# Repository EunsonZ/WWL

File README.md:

# WWL 知识库

本库帮助学习者追踪问题中的对象、关系、证据和条件：先形成可以预测现象的直觉，再理解推导或论证，最后在条件改变后重新判断。数学证明、程序执行、历史解释和规范性选择各有自己的依据；学科入口保留独立的深入路线。

从一个知识域的首页进入，再按其中的课程地图（MOC）选择阅读顺序。课程正文、可运行实验与来源材料各有入口；无需按文件夹编号一次读完整个库。

按问题进入：[[00-工作台/按问题找知识|问题入口]] · 日常记录：[[00-工作台/README|工作台]] · 浏览筛选：[[00-工作台/知识目录.base|知识目录]]

先挑一个具体问题：

| 你想弄清什么 | 先读哪里，带回什么 |
| --- | --- |
| 税在商家缴，为什么买卖双方都可能承担？ | [[社会科学/40-公共政策与社会学/02-税收转移公共服务与归宿#线性供需手算\|税楔与线性供需]]：沿同一买方价、卖方价和交易量复算归宿，再检查法定责任与福利的区别。 |
| 张量中的 1.5 怎样成为可靠的位串，又怎样交给线程？ | [[计算机知识/40-并行与异构计算/80-张量跨层执行/01-同一张量从数值到线程\|同一数值的跨层路线]]：分清数学值、编码、存储和执行；需要器件层时，从文中的本库 CMOS/噪声支线继续。 |
| 工资、贷款、进口与公共决定怎样改变生活？ | [[社会科学/00-开始/01-社会认知学习路线与32个问题\|社会认知八组问题]]：选择组织、制度、税收预算、货币金融或国内外循环，不以考试年度为前置。 |

普通 Markdown 和链接提供完整阅读入口；知识目录、Bases 与 Canvas 只是可选视图。

如果你想把机器学习、系统与算法的基础连成一条可返回的阅读路径，使用 [[00-工作台/基础理论学习路线|基础理论学习路线]]；它只帮你选择下一页，不把阅读次数或时间当作掌握证明。

## 从这里开始

| 知识域 | 首页 | 继续阅读 |
| --- | --- | --- |
| 数学 | [[数学/00-数学-首页\|数学首页]] | [[数学/01-数学学习路线\|学习路线]] · [[数学/02-AI数学应用索引\|AI 数学应用索引]] |
| AI | [[AI/00-开始/00-AI-首页\|AI 首页]] | [[AI/00-开始/05-问题驱动知识图谱与难点导航\|按问题寻找入口]] · [[AI/80-实践/00-AI实践-MOC\|实践地图]] |
| 计算机知识 | [[计算机知识/00-开始/00-计算机知识-首页\|计算机首页]] | [[计算机知识/00-开始/全局导航/00-总学习地图\|总学习地图]] · [[计算机知识/Kali/00-导航与方法/00-Kali知识地图\|Kali 知识地图]] |
| 编程知识 | [[编程知识/00-开始/00-编程知识-首页\|编程知识首页]] | [[编程知识/10-基础/01-正则表达式/00-正则表达式-MOC\|正则表达式]]；语言系统课程从计算机首页进入 |
| 哲学与文化 | [[哲学与文化/00-开始/00-哲学与文化-首页\|哲学与文化首页]] | [[哲学与文化/10-主题/01-文化政治与组织结构/00-文化政治与组织结构-MOC\|文化政治与组织结构]] |
| 社会科学 | [[社会科学/00-开始/00-社会科学-首页\|社会科学首页]] | [[社会科学/20-经济流动与宏观/00-经济流动与宏观-MOC\|经济流动与宏观]] · [[社会科学/30-金融市场与风险/00-金融市场与风险-MOC\|金融市场与风险]] · [[社会科学/40-公共政策与社会学/00-公共政策与社会学-MOC\|公共政策与社会学]] |
| 物理 | [[物理/00-开始/00-物理-首页\|物理首页]] | [[物理/20-电磁学/00-电磁学-MOC\|场源与边值]] · [[物理/30-电动力学/00-电动力学-MOC\|守恒源与因果场]] · [[物理/40-量子力学/00-量子力学-MOC\|态、谱与测量]] · [[物理/50-半导体物理/00-半导体物理-MOC\|晶体、占据与输运]] |
| 电子电路 | [[电子电路/00-开始/00-电子电路-首页\|电子电路首页]] | [[电子电路/10-电路基础/00-电路基础-MOC\|单位、KCL与RC]] · [[电子电路/00-开始/01-电子电路课程地图与覆盖边界\|E01–E12分层范围]] · [[电子电路/10-电路基础/00-电路基础-MOC#从五课接到器件与模拟\|五课后进入器件与模拟]] · [[电子电路/20-器件与模拟/01-PN结与二极管工作点\|旧版二极管工作点速查]] |
| 信号与系统 | [[信号与系统/00-开始/00-信号与系统-首页\|信号与系统首页]] | [[信号与系统/10-连续与离散系统/00-连续与离散系统-MOC\|对象、卷积、ROC与采样]] · [[信号与系统/00-开始/01-信号系统课程地图与覆盖边界\|S01–S14与控制方向]] · [[信号与系统/20-数字信号处理/01-FIR滤波设计与频率规格\|滤波与流式]] · [[信号与系统/30-随机信号与推断/01-随机过程相关与功率谱\|随机谱与检测]] |
| 控制论 | [[控制论/00-控制论-MOC\|控制课程入口]] | [[控制论/00-开始/01-控制课程路线与覆盖边界\|调节起点与课程路线]] · [[控制论/10-系统课程/01-调节目标信息与行动#先做一个无需微积分的诊断\|信息、动作与合格目标]] · [[控制论/10-系统课程/02-热模型从物理到连续反馈#先固定对象和每个端口\|带单位的热模型]] |
| Obsidian 知识 | [[Obsidian知识/00-开始/Welcome\|Obsidian 教学首页]] | [[Obsidian知识/00-开始/00-Playground-首页\|练习地图]] · [[Obsidian知识/00-开始/02-30分钟快速上手\|30 分钟上手]] |

各知识域保留基础和深入路径；Obsidian 是阅读、记录与工具支撑层。物理四课从各自已建段落进入，电子路线继续承担端口、器件与工程近似；各域剩余课程、专业工具、设备和真人证据按对应正文分别判断。

## 实践、材料与任务

- 计算机实验与图示：[[计算机知识/00-开始/全局导航/09-本地实验与验证入口|实验入口]]、[[计算机知识/00-开始/全局导航/08-本地图示索引|图示索引]]。
- 数学资源与记号：[[数学/90-资源/00-数学资源-MOC|数学资源地图]]。
- 哲学原始材料及两份稿件：[[哲学与文化/90-资源/01-原始材料与参考来源索引|来源索引]]；[[Clippings/分析文化政治影响|原始对话]]。
- 书籍与历史个人资料：[[资料/README|资料总索引]]；数学、物理、电子与信号、钢琴书籍及个人规划分区阅读。
- 双来源原稿：[[Clippings/WorkWithLLM/原稿索引|WorkWithLLM 对话与草稿]]、[[Clippings/AGoodStart101/原稿索引|AGoodStart101 教程与剪藏]]。
- 已有任务工作区：[[TaskNotes/Start Here|TaskNotes 入口]]。

## 维护与阅读说明

日常使用不需要管理 agents。把具体卡点交给 AI 即可，例如“这页的公式怎样代入”“两篇解释是不是矛盾”“我记得这个概念，但找不到”。AI 负责定位、必要分工、证据与检查，不要求你维护任务表。

知识维护见 [[00-工作台/维护指南|维护指南]]；多人交接、模型与费用见 [[00-工作台/并行协作与模型路由|并行协作与模型路由]]；AI 的稳定入口是 [[AGENTS|协作约定]]。插件日常与按需使用见 [[00-工作台/插件取舍|插件取舍]]，实际改进、验证和未决项从 [[CHANGES|CHANGES.md]] 进入。

[[NewAgents|旧手册入口]] 只供追溯。当前建设与未决项从 [任务总入口 #224](https://github.com/EunsonZ/WWL/issues/224) 进入对应议题，目录整理由 [#251](https://github.com/EunsonZ/WWL/issues/251) 接续；旧执行单和规划按固定提交追溯。历史交付只证明当时明示的范围，不替当前快照认证。

资料书目中的“本包未提供”表示附件不在上传快照中，不能用空文件冒充恢复。内容可读、证据已核验、个人已掌握是不同状态；并行数量也不是质量证明。

## 历史导入与结构记录

- 双来源增量导入、保全与验证范围见 [[Logs/2026-09-08_双来源知识增量导入/验收记录|增量导入验收记录]]。
- 前一批目录变更、历史路径和缺失材料见 [[Logs/2026-09-08_TBM结构整理/验收记录|结构整理记录]]。
- 历史说明中的“本库未收录”表示原引用的材料不在当时库中，原目标保留以便追溯；历史报告只说明对应快照。

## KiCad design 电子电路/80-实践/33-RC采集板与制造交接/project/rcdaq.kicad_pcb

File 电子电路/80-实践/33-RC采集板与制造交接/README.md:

---
stage: 2
aliases: []
sources:
  - https://docs.kicad.org/9.0/en/cli/cli.html
  - https://dev-docs.kicad.org/en/file-formats/sexpr-schematic/
prerequisites:
  - "[[电子电路/50-PCB布局与调试/01-符号引脚封装与BOM替代#先确定电路，再决定空间]]"
  - "[[电子电路/50-PCB布局与调试/05-KiCad项目到制造包与人工复核#ERC和DRC回答不同问题]]"
---
# RCDAQ-P1：同一板、不同证据层

基础入口按J1→R1→OUT→C1/R2→GND手算1V加载；快进入口核21焊盘、4网、27前层segments、5地via的几何图与采样电荷/频率阻抗边界。全部模型和图对应同一原创40×30mm无源板，ADC在J2外部，没有假装板上IC/MCU存在。

## 文件与版本

board.json是教学坐标/引脚/路由合同；project有rcdaq.kicad_pro/sch/pcb，自有symbol/footprint库与librarytables、rcdaq.net、bom.csv/testpoints.csv、fabrication-checklist。原生格式候选可编辑但本机未发现kicad-cli，真实软件parse/save、ERC/DRC、B.Cu填区、Gerber/钻孔导出尚未运行。CPU解析只是有限s-expression字段与网集核对。采购MPN全部UNSELECTED；自有0805等几何尚未经实际MPN/厂商规则核，不能送厂。教学源文件generator标wwl_pcb1，未伪装成eeschema/pcbnew写出的工具产物。

源pcb_model.py/test_pcb_model.py/generate_figures.py各只一真源，不创建重复code-sync副本；原库与他人源码未动。SVG是真源生成输出，360/425PNG从同SVG渲染，图是原创教学模型，不是实际CAD截图/照片/仪器读数。

## 有限API及物理合同

模型只接受Python原生int/float实数，拒bool/complex/数组/cast对象及非有限；先校验再算，不静默丢虚部。标量支持域刻意有限：t0..100s、source/initial0..3.3V、R/load/probe1..1e9/1e12Ω、C1pF..10mF。rc保持v(0)=initial，expm1计算小时间步，明确load与probe并联；返回V、τ(s)、pole(Hz)、gain无量纲，t非常大视为稳态指数衰减。

sharing/coupling按指定初态电荷守恒，不是实测ADC参数；内部C1fF..1mF、crossC1fF..1μF，外C1pF..10mF，电压/edge±3.3V合同分别校验。loop f0..1GHz、L0..1mH、ΔI±1A、edge1ps..1s、R0..1MΩ；decap f1..1GHz、C1pF..10mF、ESR0..1MΩ、ESL1fH..1mH，返回阻抗实/虚/幅及理想自谐振、容量与ESR项。模型域只保证计算有限，不证明任意参数可物理实现；同一L不能重复算入元件/线路，图2/20nH为假设非提取。energy最多32个有限C、V≤3.3V，只算本板电容不包含外电源/线缆。

geometry只收原生dict/list坐标和有限标签：最多128pads、64via、8nets、每网≤64paths/每path≤64points，总segments≤512、正交非零路径；板内范围.5..39.5×.5..29.5mm。输出中心线异网交叉、按本教学焊盘尺寸的异网接近、明确图连接。GND把via及THT GND视为矩形B.Cu连续面锚点，这是**模型假设**，实际zone未填；不替代ERC/DRC、铜多边形/热焊盘/最小孔距/EM场。所有图算法迭代有固定预算，没有浮点while找收敛。

## 运行方法

复制完整实验到库外新目录。两个CLI必须显式--output，缺参exit2不写caller/MPL/XDG；导入不解析argv，不写、不初始化绘图/字体，不改PRNG。generate(output)与main(argv=None)可显式调用。数值stdlib；图仅在generate内部lazy import已有matplotlib/CairoSVG，direct Figure、rc_context，MPL/XDG缓存限定输出下并恢复环境；成功/绘图异常均恢复环境与rcParams，缺依赖not_run、不安装。

```bash
python -B -m unittest discover -s . -p test_pcb_model.py -v
python -B pcb_model.py --output /private/tmp/rcdaq-my-numeric
python -B generate_figures.py --output /private/tmp/rcdaq-my-figures
```

results.json和assets/figure-data.json分别标SI电路及mm几何，RC R1k/C1u/RL10k，初值.4V。板图按同board.json引用与坐标，不追求虚假真实照片。改CAD应同步引脚网表/BOM/testpoints及模型版本，比较修改的来源，不把旧hash的结果当新板结果。

## 工具和实物的验收接口

正文05给真实KiCad9可执行命令及制造清单，正式执行须记录工具版本、输入SHA、原始输出、parity/填区和人工复核。教学CAD没有供应商批准的制造参数或可采购BOM。仪器接地、限流计划与故障树在正文06；实际上电/探针/照片/硬件测量都未跑。

V35贡献为连续/分割回流、F/B剖面、GNDvia、外ADC去耦真实闭环与明确基带/边沿频段；资格待独审。V37只有同板原理图/布局/TP和安全计划，缺同板授权照片/实物仪器证据，partial。未消费ArduinoUno/photo线索，也未借单元件照片拼凑同板。X13仅解释有限RLC/频率模型边界，不签完整场/PDE桥。SPICE/EM提取/KiCad/UI/ERC/DRC/manufacture/Gerberviewer/hardware/humanlearning均not_run。

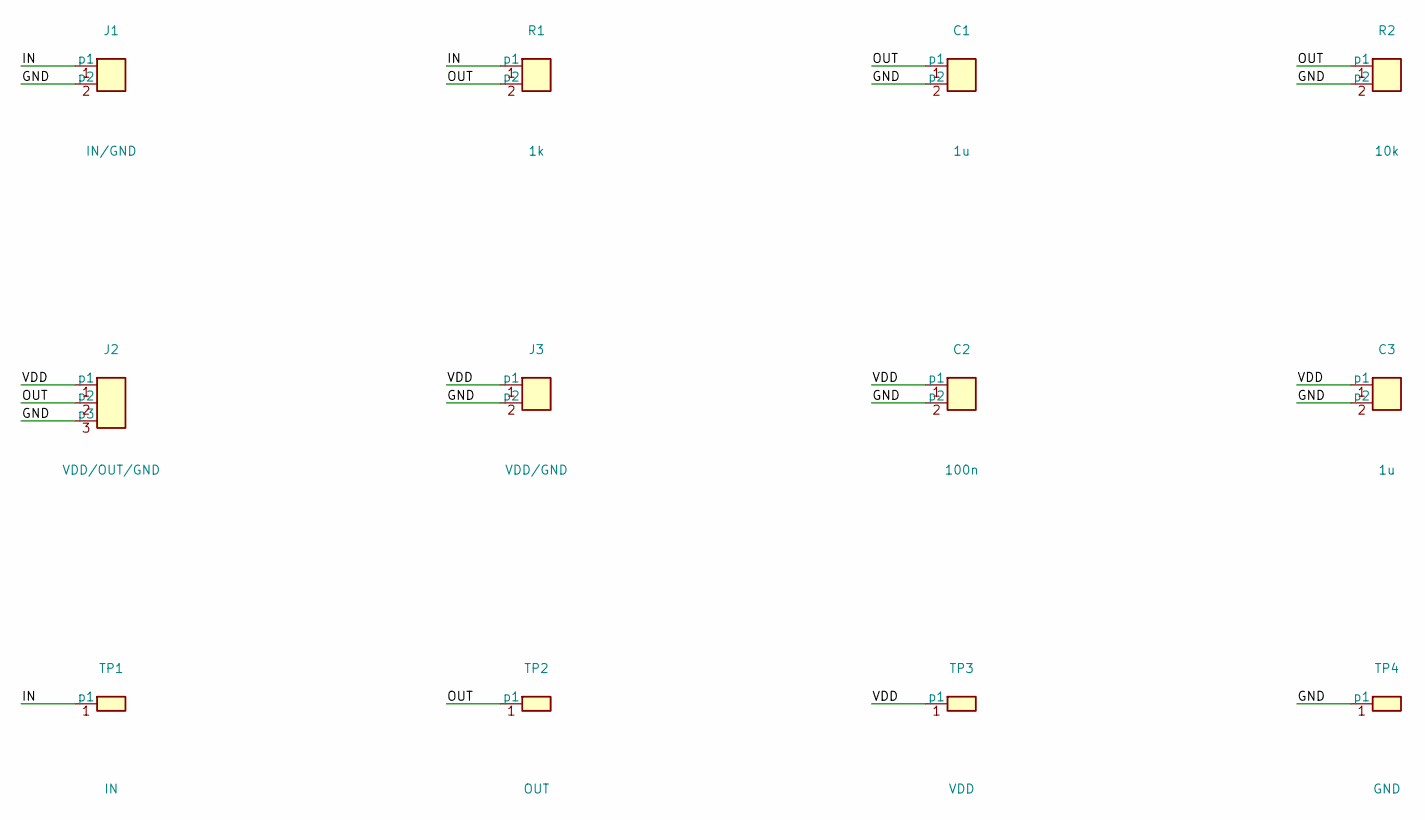
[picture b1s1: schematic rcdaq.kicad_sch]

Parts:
C1, C3: 1u; Passive0805
C2: 100n; Passive0805
J1: IN/GND; Header2
J2: VDD/OUT/GND; Header3
J3: VDD/GND; Header2
R1: 1k; Passive0805
R2: 10k; Passive0805
TP1: IN; TestPad
TP2: OUT; TestPad
TP3: VDD; TestPad
TP4: GND; TestPad

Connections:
GND: C1.2 (p2), C2.2 (p2), C3.2 (p2), J1.2 (p2), J2.3 (p3), J3.2 (p2), R2.2 (p2), TP4.1
IN: J1.1 (p1), R1.1 (p1), TP1.1
OUT: C1.1 (p1), J2.2 (p2), R1.2 (p2), R2.1 (p1), TP2.1
VDD: C2.1 (p1), C3.1 (p1), J2.1 (p1), J3.1 (p1), TP3.1

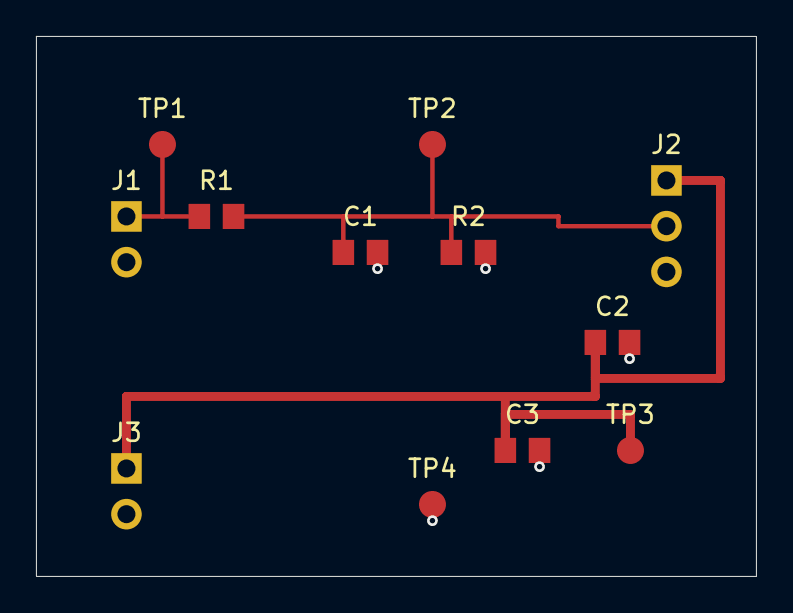
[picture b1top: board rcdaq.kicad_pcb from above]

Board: 2 copper layers, 40.0 x 30.0 mm, 12 parts (0 on the bottom side), 4 nets.

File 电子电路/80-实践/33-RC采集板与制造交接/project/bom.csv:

ref,value,footprint,population,vendor_MPN,qualification_required
J1,IN/GND,PCBTeaching:Header2,populate,UNSELECTED,pin1/drawing/rating/tolerance/DCbias/lifecycle; teaching only
R1,1k,PCBTeaching:Passive0805,populate,UNSELECTED,pin1/drawing/rating/tolerance/DCbias/lifecycle; teaching only
C1,1u,PCBTeaching:Passive0805,populate,UNSELECTED,pin1/drawing/rating/tolerance/DCbias/lifecycle; teaching only
R2,10k,PCBTeaching:Passive0805,populate,UNSELECTED,pin1/drawing/rating/tolerance/DCbias/lifecycle; teaching only
J2,VDD/OUT/GND,PCBTeaching:Header3,populate,UNSELECTED,pin1/drawing/rating/tolerance/DCbias/lifecycle; teaching only
J3,VDD/GND,PCBTeaching:Header2,populate,UNSELECTED,pin1/drawing/rating/tolerance/DCbias/lifecycle; teaching only
C2,100n,PCBTeaching:Passive0805,populate,UNSELECTED,pin1/drawing/rating/tolerance/DCbias/lifecycle; teaching only
C3,1u,PCBTeaching:Passive0805,populate,UNSELECTED,pin1/drawing/rating/tolerance/DCbias/lifecycle; teaching only
TP1,IN,PCBTeaching:TestPad,populate,UNSELECTED,pin1/drawing/rating/tolerance/DCbias/lifecycle; teaching only
TP2,OUT,PCBTeaching:TestPad,populate,UNSELECTED,pin1/drawing/rating/tolerance/DCbias/lifecycle; teaching only
TP3,VDD,PCBTeaching:TestPad,populate,UNSELECTED,pin1/drawing/rating/tolerance/DCbias/lifecycle; teaching only
TP4,GND,PCBTeaching:TestPad,populate,UNSELECTED,pin1/drawing/rating/tolerance/DCbias/lifecycle; teaching only
